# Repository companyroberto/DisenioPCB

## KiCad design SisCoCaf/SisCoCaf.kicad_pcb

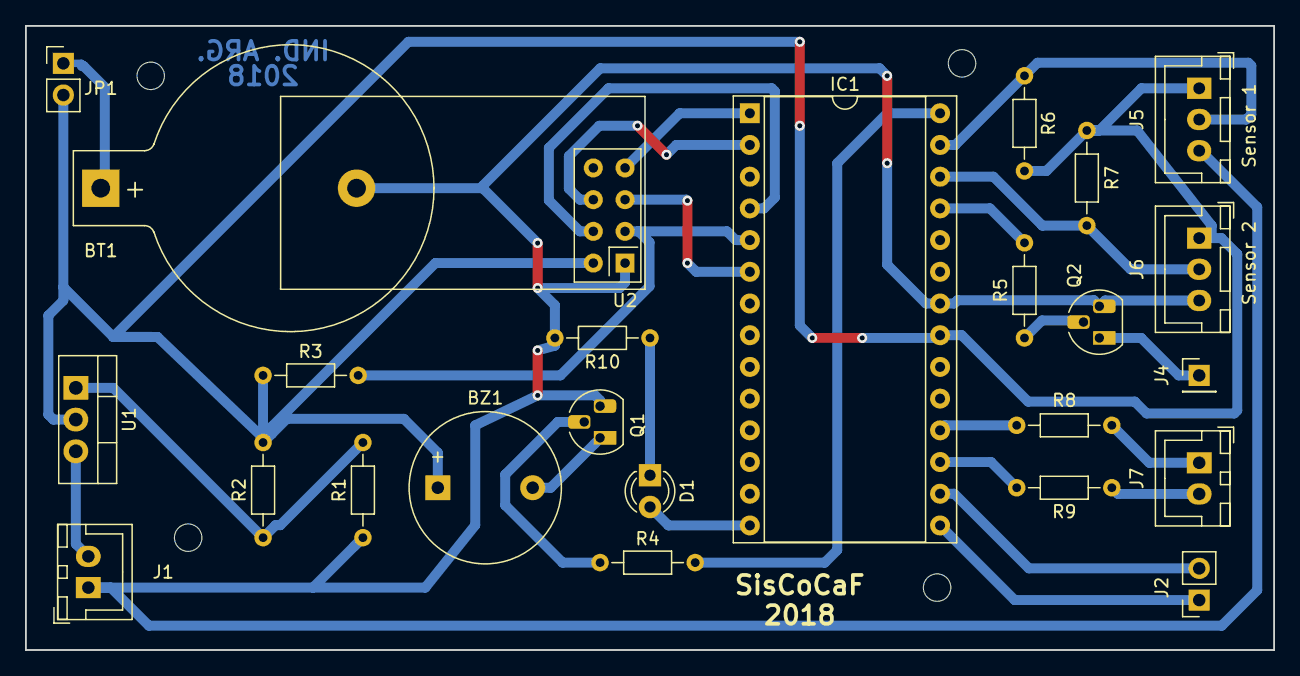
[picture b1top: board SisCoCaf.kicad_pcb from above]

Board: 2 copper layers, 100.0 x 50.0 mm, 29 parts (0 on the bottom side), 26 nets.

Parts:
BT1: Battery_Cell; BatteryHolder_Keystone_103_1x20mm
BZ1: Buzzer; Buzzer_12x9.5RM7.6
D1: LED; LED_D3.0mm
IC1: LPC111X_102; DIP-28_W15.24mm_Socket
J1: Entrada; JST_XH_B02B-XH-A_1x02_P2.50mm_Vertical
J2: Conn_01x02_Female; PinSocket_1x02_P2.54mm_Vertical
J4: Conn_01x01_Male; PinHeader_1x01_P2.54mm_Vertical
J5, J6: Conn_01x03_Male; JST_XH_B03B-XH-A_1x03_P2.50mm_Vertical
J7: Conn_01x02_Male; JST_XH_B02B-XH-A_1x02_P2.50mm_Vertical
JP1: Jumper; PinHeader_1x02_P2.54mm_Vertical
MH1, MH2, MH3, MH4: MountingHole; MountingHole_2.2mm_M2
Q1, Q2: BC547; TO-92_HandSolder
R1, R2: 1k; R_Axial_DIN0204_L3.6mm_D1.6mm_P7.62mm_Horizontal
R3: 5k6; R_Axial_DIN0204_L3.6mm_D1.6mm_P7.62mm_Horizontal
R4, R5, R8, R9, R10: 220; R_Axial_DIN0204_L3.6mm_D1.6mm_P7.62mm_Horizontal
R6, R7: 4k7; R_Axial_DIN0204_L3.6mm_D1.6mm_P7.62mm_Horizontal
U1: LM317_TO39; TO-220-3_Vertical
U2: NRF24L01_Breakout; nRF24L01_Breakout

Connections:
+12V: J1.2, U1.3
/BUZZER: IC1.28, R4.2
/EntradaD1: IC1.18, R8.2
/EntradaD2: IC1.17, R9.2
/LED: D1.2, IC1.14
/RX: IC1.15, J2.1
/SalidaD1: IC1.25, R5.2
/Sensor1: IC1.27, J5.2, R6.1
/Sensor2: IC1.26, J6.2, R7.1
/TX: IC1.16, J2.2
GND: BT1.2, IC1.22, J1.1, J5.3, J6.3, Q1.3, Q2.3, R1.1, R10.2, U2.1
unnamed: BT1.1, JP1.1
unnamed: BZ1.2, Q1.1
unnamed: D1.1, R10.1
unnamed: IC1.1, U2.7
unnamed: IC1.2, U2.6
unnamed: IC1.4, U2.4
unnamed: IC1.5, R3.2, U2.3
unnamed: IC1.6, U2.5
unnamed: J4.1, Q2.1
unnamed: J7.1, R8.1
unnamed: J7.2, R9.1
unnamed: Q1.2, R4.1
unnamed: Q2.2, R5.1
unnamed: R1.2, R2.1, U1.1
VDD: BZ1.1, IC1.21, J5.1, J6.1, JP1.2, R2.2, R3.1, R6.2, R7.2, U1.2, U2.2

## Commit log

2018-09-07 SisCoCaf commit
2018-09-08 tourK5 commit
2018-10-19 Listo para revisión del esquemático
2018-10-20 Agrego huellas
2018-10-20 Incorporar pila y jumper
2018-11-12 Esquemático corregido. PCB v1.0
2018-11-13 Esquemático y PCB terminados.
    En espera de revisión por el profesor.
2018-11-16 Asigno datasheet al LPC
2018-11-16 Modificando simbolos
2018-11-28 Versión final
    Aplico correcciones indicadas por profesor.
2018-11-28 Versión final.
    Realizo correcciones indicadas por profesor.

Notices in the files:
SisCoCaf/SisCoCaf.kicad_pcb:
Licencia Creative Commons
